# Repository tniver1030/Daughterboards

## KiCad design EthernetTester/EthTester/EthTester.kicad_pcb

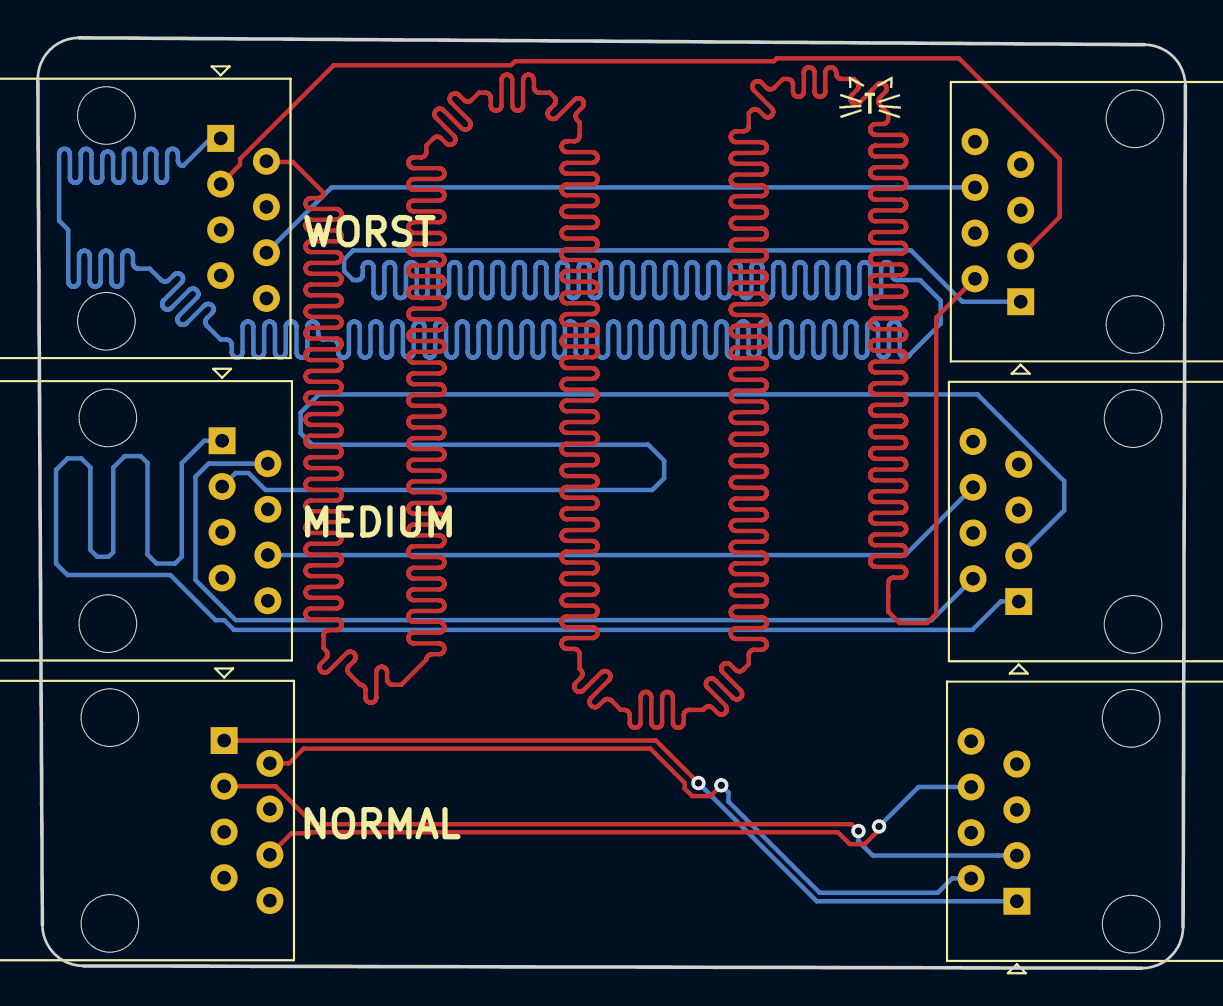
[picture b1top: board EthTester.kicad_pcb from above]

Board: 2 copper layers, 63.8 x 51.7 mm, 6 parts (0 on the bottom side), 12 nets.

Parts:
J1, J2, J3, J4, J5, J6: RJ45; RJ45_Amphenol_54602-x08_Horizontal

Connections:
unnamed: J1.1, J4.1
unnamed: J1.2, J4.2
unnamed: J1.3, J4.3
unnamed: J1.6, J4.6
unnamed: J2.1, J5.1
unnamed: J2.2, J5.2
unnamed: J2.3, J5.3
unnamed: J2.6, J5.6
unnamed: J3.1, J6.1
unnamed: J3.2, J6.2
unnamed: J3.3, J6.3
unnamed: J3.6, J6.6
